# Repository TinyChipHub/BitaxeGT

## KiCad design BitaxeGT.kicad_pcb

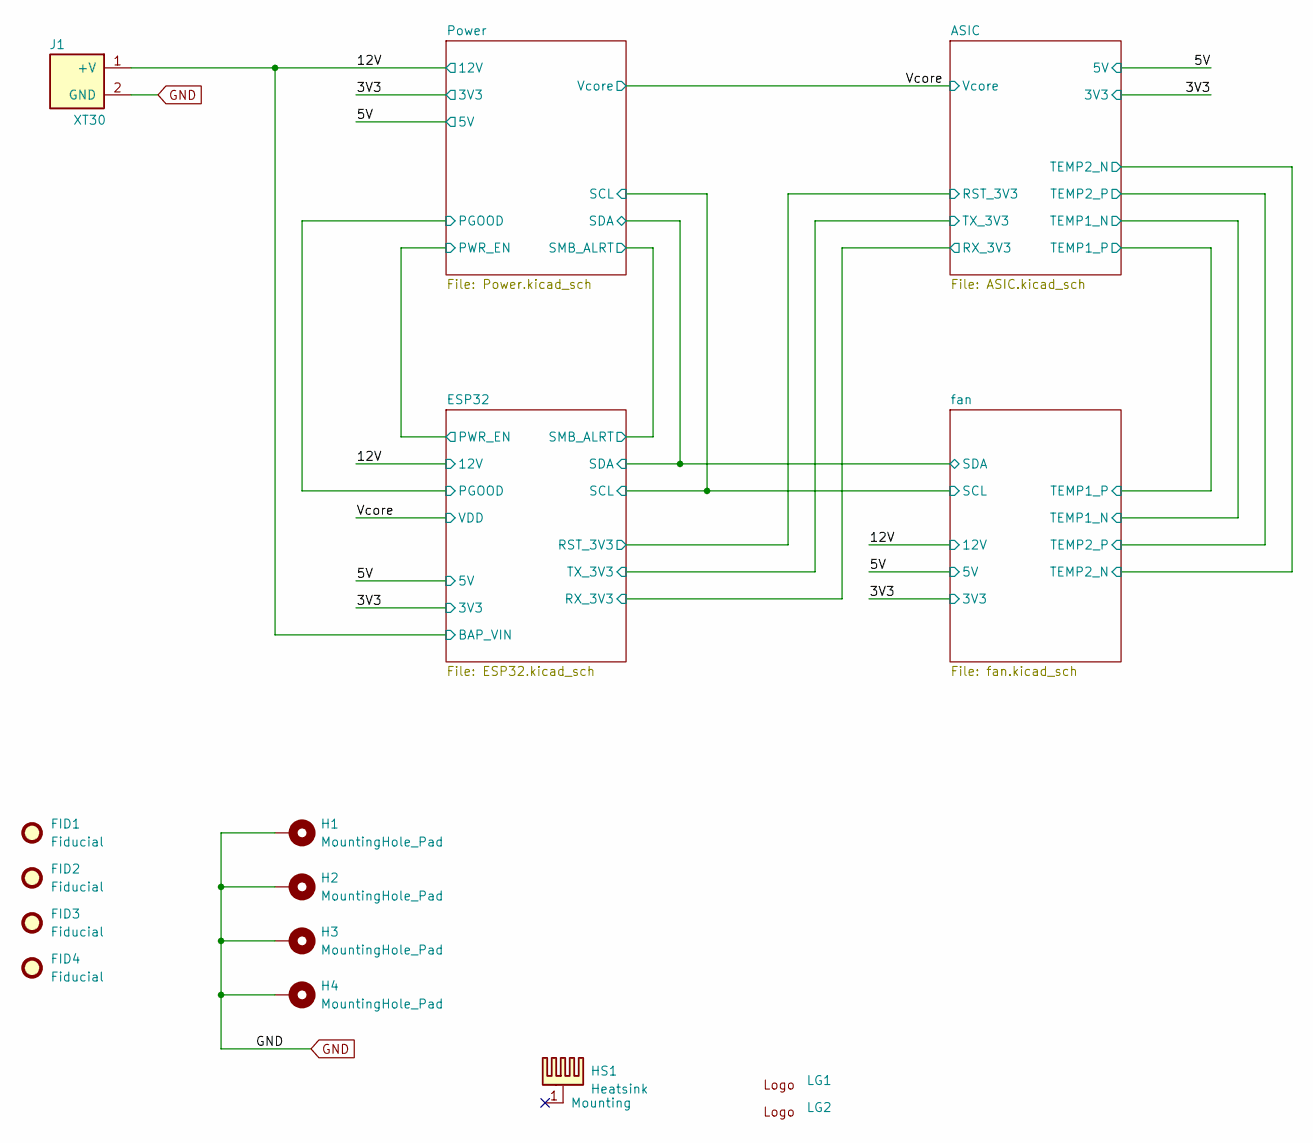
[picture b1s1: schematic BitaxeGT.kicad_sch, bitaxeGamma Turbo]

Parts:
FID1, FID2, FID3, FID4: Fiducial; Fiducial_1mm_Mask2mm
H1, H2, H3, H4: MountingHole_Pad; MountingHole_3.2mm_M3_Pad_Via
HS1: Heatsink; Heatsink-BitaxeGT
J1: XT30; XT30PW-M; PARTNO XT30PW-M; LCSC C431092
LG1: TCH-Logo
LG2: TCH-Logo-Mask

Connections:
/12V: J1.1 (+V); also elsewhere on the board
GND: H1.1, H2.1, H3.1, H4.1, J1.2 (GND); also elsewhere on the board

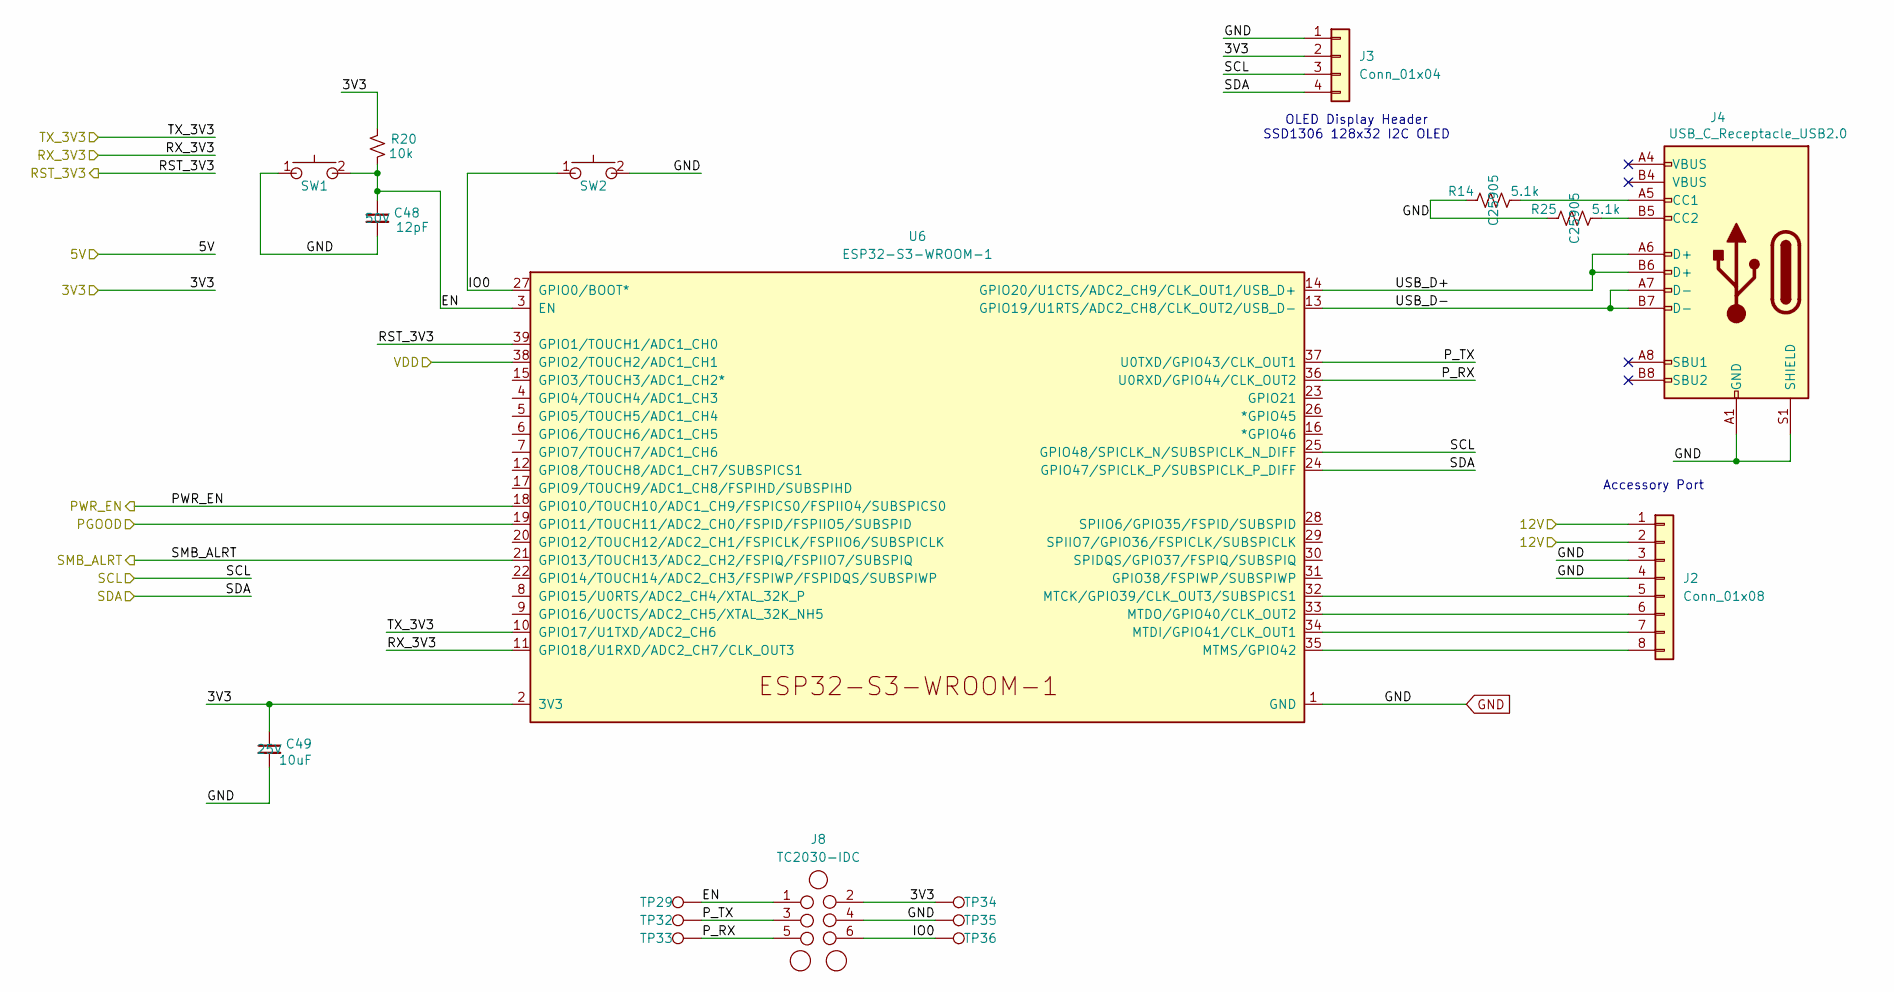
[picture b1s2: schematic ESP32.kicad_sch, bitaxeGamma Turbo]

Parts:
C48: 12pF; C_0402_1005Metric; Voltage 50V; PARTNO CC0402JRNPO9BN120; LCSC C106201
C49: 10uF; C_0603_1608Metric; Voltage 25V; PARTNO GRM188R61E106KA73D; LCSC C344022
J2: Conn_01x08; FPC-SMD_P0.50-8P_FGS-XJ-H2.0; PARTNO FFC2B35-08-T; LCSC C262657
J3: Conn_01x04; PinHeader_1x04_P2.54mm_Vertical_shifted
J4: USB_C_Receptacle_USB2.0; USB_C_Receptacle_GCT_USB4105-xx-A; PARTNO USB4105-GF-A; LCSC C2982555
J8: TC2030-IDC; Tag-Connect_TC2030-IDC-NL_2x03_P1.27mm_Vertical
R14, R25: 5.1k; R_0402_1005Metric; PARTNO RMCF0402JT5K10; LCSC C25905
R20: 10k; R_0402_1005Metric; PARTNO RC0402JR-0710KL; LCSC C60489
SW1, SW2: SWITCH-SPST; SW_TL3330AF130QG_EWI; PARTNO TL3330AF130QG; LCSC C2886885
TP29, TP32, TP33, TP34, TP35, TP36: TestPoint; TestPoint_Pad_D1.5mm
U6: ESP32-S3-WROOM-1; PARTNO ESP32-S3-WROOM-1-N16R8; LCSC C2913202

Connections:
/3V3: C49.1, J3.2, J8.2, R20.2, TP34.1, U6.2 (3V3); also elsewhere on the board
/12V: J2.1, J2.2; also elsewhere on the board
/ASIC/RST_3V3: U6.39 (GPIO1/TOUCH1/ADC1_CH0); also elsewhere on the board
/ASIC/RX_3V3: U6.11 (GPIO18/U1RXD/ADC2_CH7/CLK_OUT3); also elsewhere on the board
/ASIC/TX_3V3: U6.10 (GPIO17/U1TXD/ADC2_CH6); also elsewhere on the board
/ESP32/EN: C48.1, J8.1, R20.1, SW1.2, TP29.1, U6.3 (EN)
/ESP32/IO0: J8.6, SW2.1, TP36.1, U6.27 (GPIO0/BOOT*)
/ESP32/PWR_EN: U6.18 (GPIO10/TOUCH10/ADC1_CH9/FSPICS0/FSPIIO4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)
/ESP32/P_RX: J8.5, TP33.1, U6.36 (U0RXD/GPIO44/CLK_OUT2)
/ESP32/P_TX: J8.3, TP32.1, U6.37 (U0TXD/GPIO43/CLK_OUT1)
/ESP32/SCL: J3.3, U6.25 (GPIO48/SPICLK_N/SUBSPICLK_N_DIFF); also elsewhere on the board
/ESP32/SDA: J3.4, U6.24 (GPIO47/SPICLK_P/SUBSPICLK_P_DIFF); also elsewhere on the board
/ESP32/SMB_ALRT: U6.21 (GPIO13/TOUCH13/ADC2_CH2/FSPIQ/FSPIIO7/S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); also elsewhere on the board
/ESP32/USB_D+: J4.A6 (D+), J4.B6 (D+), U6.14 (GPIO20/U1CTS/ADC2_CH9/CLK_OUT1/USB_D+)
/ESP32/USB_D-: J4.A7 (D-), J4.B7 (D-), U6.13 (GPIO19/U1RTS/ADC2_CH8/CLK_OUT2/USB_D-)
/Power/PGOOD: U6.19 (GPIO11/TOUCH11/ADC2_CH0/FSPID/FSPIIO5/S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); also elsewhere on the board
/Vcore: U6.38 (GPIO2/TOUCH2/ADC1_CH1); also elsewhere on the board
GND: C48.2, C49.2, J2.3, J2.4, J3.1, J4.A1 (GND), J4.B1 (GND), J4.S1 (SHIELD), J8.4, R14.1, R25.1, SW1.1, SW2.2, TP35.1, U6.1 (GND), U6.40 (GND), U6.41 (GND); also elsewhere on the board
unnamed: J2.5, U6.32 (MTCK/GPIO39/CLK_OUT3/SUBSPICS1)
unnamed: J2.6, U6.33 (MTDO/GPIO40/CLK_OUT2)
unnamed: J2.7, U6.34 (MTDI/GPIO41/CLK_OUT1)
unnamed: J2.8, U6.35 (MTMS/GPIO42)
unnamed: J4.A5 (CC1), R14.2
unnamed: J4.B5 (CC2), R25.2

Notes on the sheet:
OLED Display Header SSD1306 128x32 I2C OLED
Accessory Port

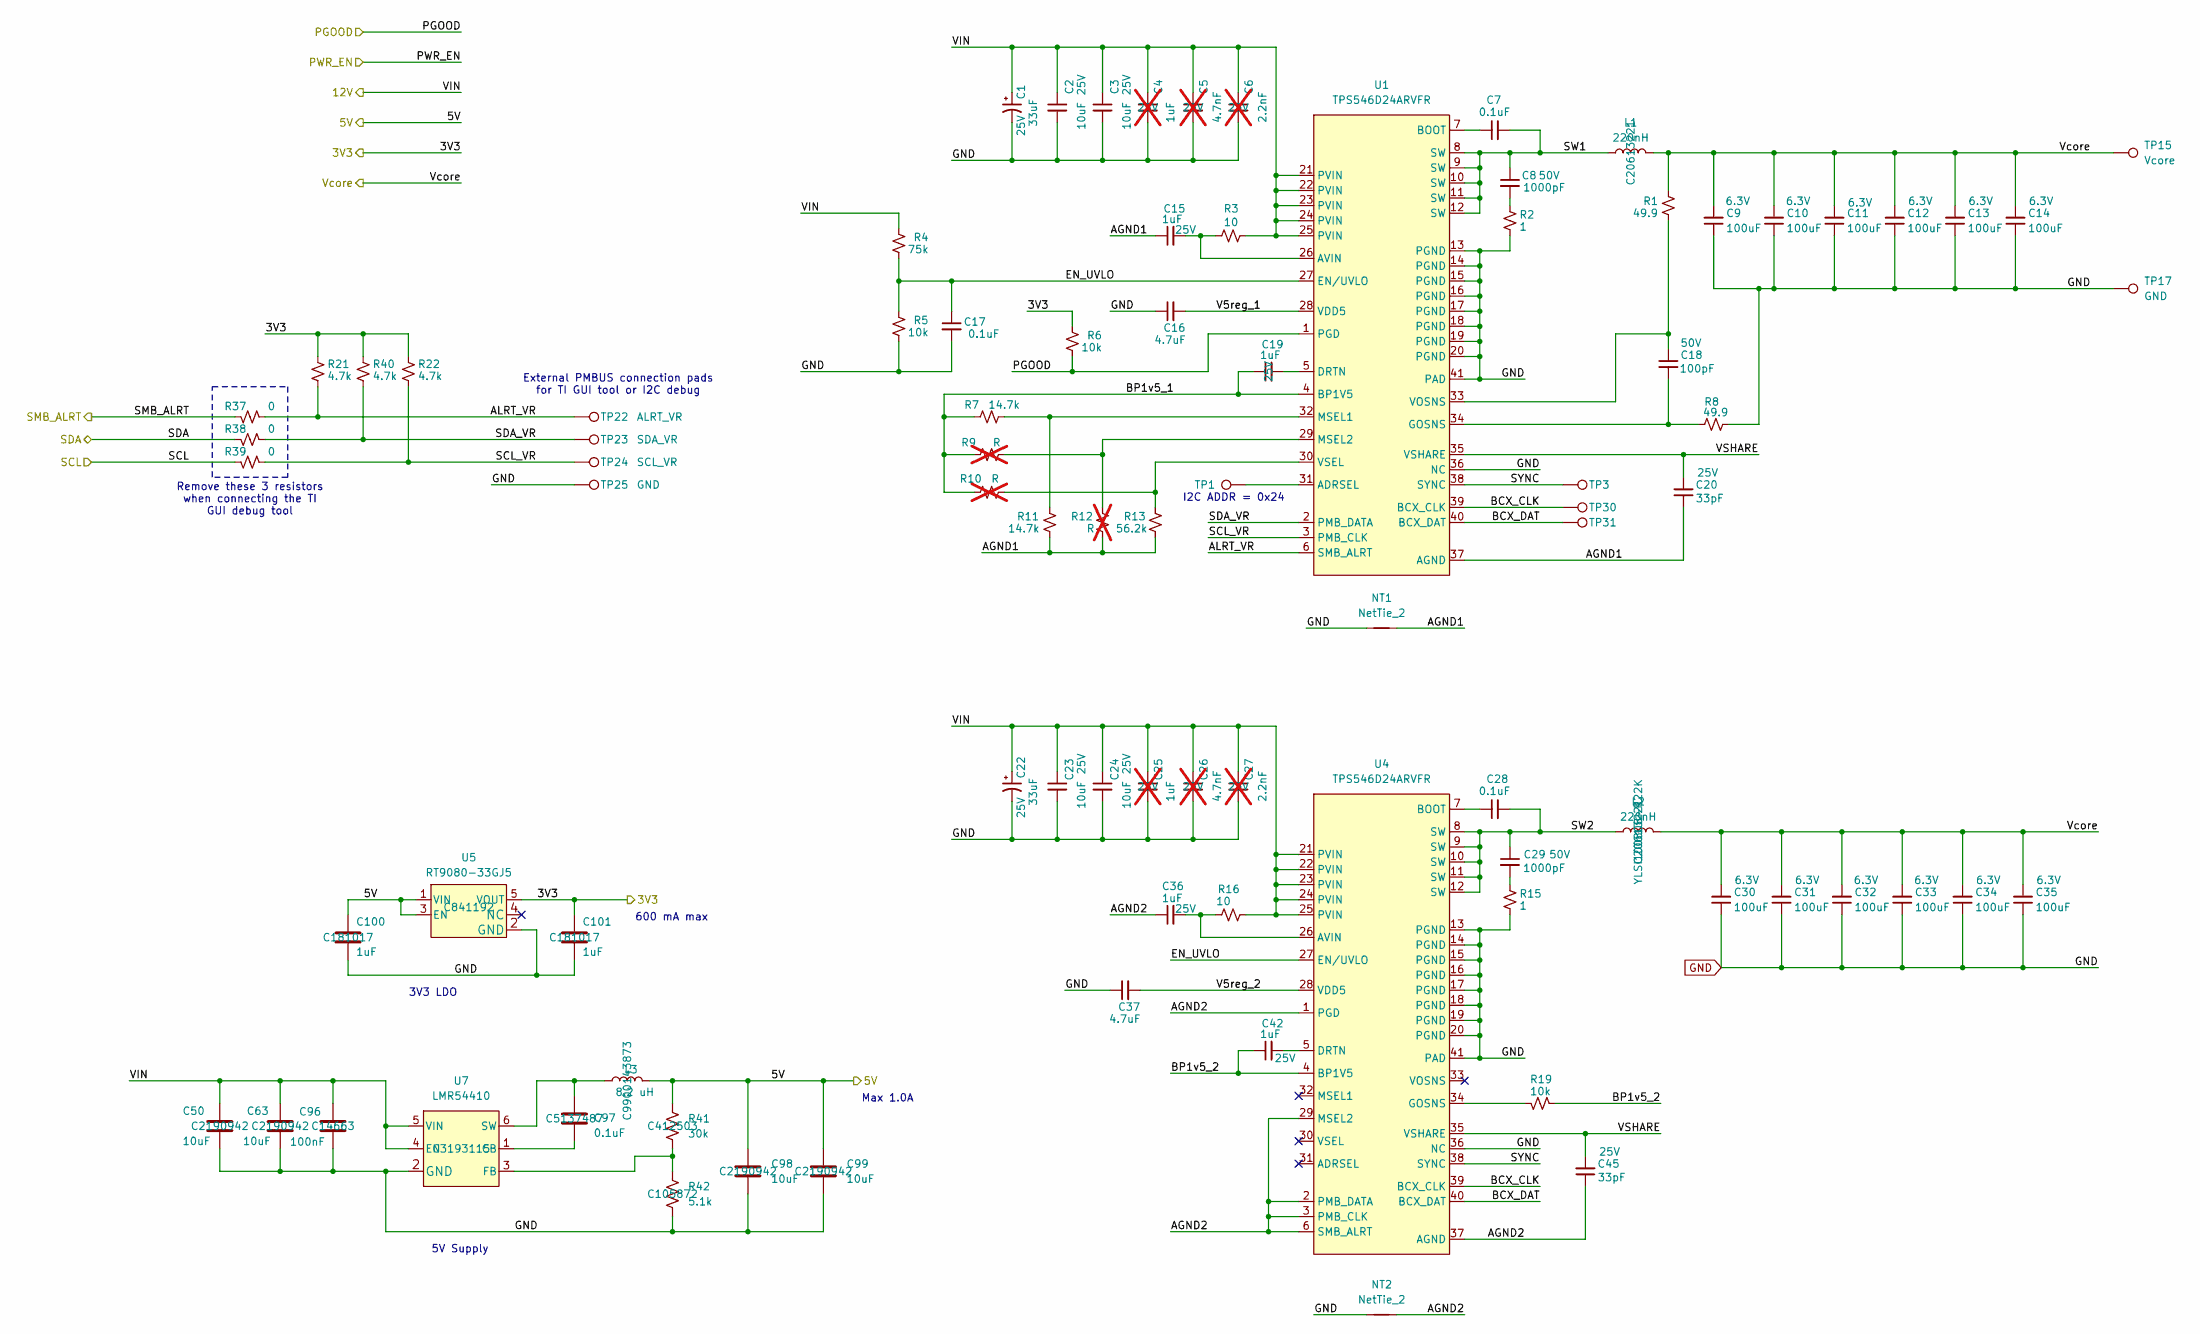
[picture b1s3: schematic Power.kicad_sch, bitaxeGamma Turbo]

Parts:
C1, C22: 33uF; CP_EIA-7343-31_Kemet-D; Voltage 25V; PARTNO T495D336K025ATE300; LCSC C122327
C2, C3, C23, C24: 10uF; C_0603_1608Metric; Voltage 25V; PARTNO GRM188R61E106KA73D; LCSC C344022
C4, C25: 1uF; C_0402_1005Metric; Voltage 25V; PARTNO TMK107B7105KA-T; not fitted
C5, C26: 4.7nF; C_0402_1005Metric; Voltage 25V; PARTNO GRM155R71E472KA01D; not fitted
C6, C27: 2.2nF; C_0402_1005Metric; Voltage 25V; PARTNO 490-8257-1-ND; not fitted
C7, C17, C28, C97: 0.1uF; C_0402_1005Metric; PARTNO KGM05AR71C104KH; LCSC C5137487
C8, C29: 1000pF; C_0805_2012Metric; Voltage 50V; PARTNO CC0805KRX7R9BB102; LCSC C46653
C9, C10, C11, C12, C13, C14, C30, C31, C32, C33, C34, C35: 100uF; C_1206_3216Metric; Voltage 6.3V; PARTNO CL31A107MQHNNNE; LCSC C15008
C15, C19, C36, C42: 1uF; C_0402_1005Metric; Voltage 25V; PARTNO TMK107B7105KA-T; LCSC C77009
C16, C37: 4.7uF; C_0402_1005Metric; PARTNO GRM155R61A475MEAAD; LCSC C23733
C18: 100pF; C_0402_1005Metric; Voltage 50V; PARTNO CC0402JRNPO9BN101; LCSC C277520
C20, C45: 33pF; C_0402_1005Metric; Voltage 25V; PARTNO KGM05ACG1E330JH; LCSC C526997
C50, C63, C98, C99: 10uF; C_0805_2012Metric; PARTNO GRM21BR61H106ME43L; LCSC C2190942
C96: 100nF; C_0603_1608Metric; PARTNO KGM15BR71H104KT; LCSC C14663
C100, C101: 1uF; C_0402_1005Metric; PARTNO EMK105BJ105MV-F; LCSC C181017
L1, L2: 220nH; SLC1175-271MEC_COC; PARTNO YLSI100808-R22K; LCSC C20613221
L3: 8.2 uH; 74438357082; PARTNO 78438357082; LCSC C9900143873
NT1, NT2: NetTie_2; NetTie-2_SMD_Pad0.2mmx1mm
R1, R8: 49.9; R_0402_1005Metric; PARTNO RC0402FR-0749R9L; LCSC C87044
R2, R15: 1; R_0805_2012Metric; PARTNO ESR10EZPJ1R0; LCSC C253344
R3, R16: 10; R_0402_1005Metric; PARTNO RC0402FR-0710RL; LCSC C138066
R4: 75k; R_0402_1005Metric; PARTNO RC0402FR-0775KL; LCSC C137935
R5, R6, R19: 10k; R_0402_1005Metric; PARTNO RC0402JR-0710KL; LCSC C60489
R7, R11: 14.7k; R_0402_1005Metric; PARTNO AC0402FR-0714K7L; LCSC C138055
R9, R10, R12: R; R_0402_1005Metric; not fitted
R13: 56.2k; R_0402_1005Metric; PARTNO RC0402FR-0756K2L; LCSC C183355
R21, R22, R40: 4.7k; R_0402_1005Metric; PARTNO RC0402JR-074K7L; LCSC C105870
R37, R38, R39: 0; R_0402_1005Metric; PARTNO RC0402JR-070RL; LCSC C60485
R41: 30k; R_0402_1005Metric; PARTNO AC0402FR-0730KL; LCSC C412503
R42: 5.1k; R_0402_1005Metric; PARTNO RC0402FR-075K1L; LCSC C105872
TP1: TestPoint; TestPoint_Pad_D1.0mm
TP3, TP30: BCX_CLK; TestPoint_Pad_D1.0mm
TP15: Vcore; TestPoint_Pad_D1.5mm
TP17, TP25: GND; TestPoint_Pad_D1.5mm
TP22: ALRT_VR; TestPoint_Pad_D1.5mm
TP23: SDA_VR; TestPoint_Pad_D1.5mm
TP24: SCL_VR; TestPoint_Pad_D1.5mm
TP31: BCX_DAT; TestPoint_Pad_D1.0mm
U1, U4: TPS546D24ARVFR; LQFN40-CLIP; PARTNO TPS546D24ARVFR; LCSC C507280
U5: RT9080-33GJ5; PARTNO RT9080-33GJ5; LCSC C841192
U7: LMR54410; SOT-23-6; PARTNO LMR54410FDBVR; LCSC C3193115

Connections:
/3V3: C101.1, R6.2, R21.1, R22.1, R40.1, U5.5 (VOUT); also elsewhere on the board
/5V: C98.1, C99.1, C100.1, L3.2, R41.1, U5.1 (VIN), U5.3 (EN); also elsewhere on the board
/12V: C1.1, C2.1, C3.1, C4.1, C5.1, C6.1, C22.1, C23.1, C24.1, C25.1, C26.1, C27.1, C50.1, C63.1, C96.2, R3.1, R4.2, R16.1, U1.21 (PVIN), U1.22 (PVIN), U1.23 (PVIN), U1.24 (PVIN), U1.25 (PVIN), U4.21 (PVIN), U4.22 (PVIN), U4.23 (PVIN), U4.24 (PVIN), U4.25 (PVIN), U7.4 (EN), U7.5 (VIN); also elsewhere on the board
/ESP32/SCL: R39.1; also elsewhere on the board
/ESP32/SDA: R38.1; also elsewhere on the board
/ESP32/SMB_ALRT: R37.1; also elsewhere on the board
/Power/AGND1: C15.1, C20.1, NT1.2, R11.2, R12.1, R13.1, U1.37 (AGND)
/Power/AGND2: C36.1, C45.1, NT2.2, U4.1 (PGD), U4.2 (PMB_DATA), U4.3 (PMB_CLK), U4.6 (SMB_ALRT), U4.29 (MSEL2), U4.37 (AGND)
/Power/ALRT_VR: R21.2, R37.2, TP22.1, U1.6 (SMB_ALRT)
/Power/BCX_CLK: TP30.1, U1.39 (BCX_CLK), U4.39 (BCX_CLK)
/Power/BCX_DAT: TP31.1, U1.40 (BCX_DAT), U4.40 (BCX_DAT)
/Power/BP1v5_1: C19.1, R7.2, R9.2, R10.2, U1.4 (BP1V5)
/Power/BP1v5_2: C42.1, R19.1, U4.4 (BP1V5)
/Power/EN_UVLO: C17.1, R4.1, R5.2, U1.27 (EN/UVLO), U4.27 (EN/UVLO)
/Power/PGOOD: R6.1, U1.1 (PGD); also elsewhere on the board
/Power/SCL_VR: R22.2, R39.2, TP24.1, U1.3 (PMB_CLK)
/Power/SDA_VR: R38.2, R40.2, TP23.1, U1.2 (PMB_DATA)
/Power/SW1: C7.2, C8.1, L1.1, U1.8 (SW), U1.9 (SW), U1.10 (SW), U1.11 (SW), U1.12 (SW)
/Power/SW2: C28.2, C29.1, L2.1, U4.8 (SW), U4.9 (SW), U4.10 (SW), U4.11 (SW), U4.12 (SW)
/Power/SYNC: TP3.1, U1.38 (SYNC), U4.38 (SYNC)
/Power/V5reg_1: C16.2, U1.28 (VDD5)
/Power/V5reg_2: C37.2, U4.28 (VDD5)
/Power/VSHARE: C20.2, C45.2, U1.35 (VSHARE), U4.35 (VSHARE)
/Vcore: C9.2, C10.2, C11.2, C12.2, C13.2, C14.2, C30.2, C31.2, C32.2, C33.2, C34.2, C35.2, L1.2, L2.2, R1.1, TP15.1; also elsewhere on the board
GND: C1.2, C2.2, C3.2, C4.2, C5.2, C6.2, C9.1, C10.1, C11.1, C12.1, C13.1, C14.1, C16.1, C17.2, C22.2, C23.2, C24.2, C25.2, C26.2, C27.2, C30.1, C31.1, C32.1, C33.1, C34.1, C35.1, C37.1, C50.2, C63.2, C96.1, C98.2, C99.2, C100.2, C101.2, NT1.1, NT2.1, R2.2, R5.1, R8.2, R15.2, R42.2, TP17.1, TP25.1, U1.13 (PGND), U1.14 (PGND), U1.15 (PGND), U1.16 (PGND), U1.17 (PGND), U1.18 (PGND), U1.19 (PGND), U1.20 (PGND), U1.36 (NC), U1.41 (PAD), U4.13 (PGND), U4.14 (PGND), U4.15 (PGND), U4.16 (PGND), U4.17 (PGND), U4.18 (PGND), U4.19 (PGND), U4.20 (PGND), U4.36 (NC), U4.41 (PAD), U5.2 (GND), U7.2 (GND); also elsewhere on the board
unnamed: C8.2, R2.1
unnamed: C29.2, R15.1
unnamed: TP1.1, U1.31 (ADRSEL)
unnamed: C15.2, R3.2, U1.26 (AVIN)
unnamed: C7.1, U1.7 (BOOT)
unnamed: C19.2, U1.5 (DRTN)
unnamed: C18.2, R8.1, U1.34 (GOSNS)
unnamed: R7.1, R11.1, U1.32 (MSEL1)
unnamed: R9.1, R12.2, U1.29 (MSEL2)
unnamed: C18.1, R1.2, U1.33 (VOSNS)
unnamed: R10.1, R13.2, U1.30 (VSEL)
unnamed: C36.2, R16.2, U4.26 (AVIN)
unnamed: C28.1, U4.7 (BOOT)
unnamed: C42.2, U4.5 (DRTN)
unnamed: R19.2, U4.34 (GOSNS)
unnamed: C97.2, U7.1 (CB)
unnamed: R41.2, R42.1, U7.3 (FB)
unnamed: C97.1, L3.1, U7.6 (SW)

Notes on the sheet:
External PMBUS connection pads for TI GUI tool or I2C debug
Max 1.0A
3V3 LDO
Remove these 3 resistors when connecting the TI GUI debug tool
I2C ADDR = 0x24
600 mA max
5V Supply

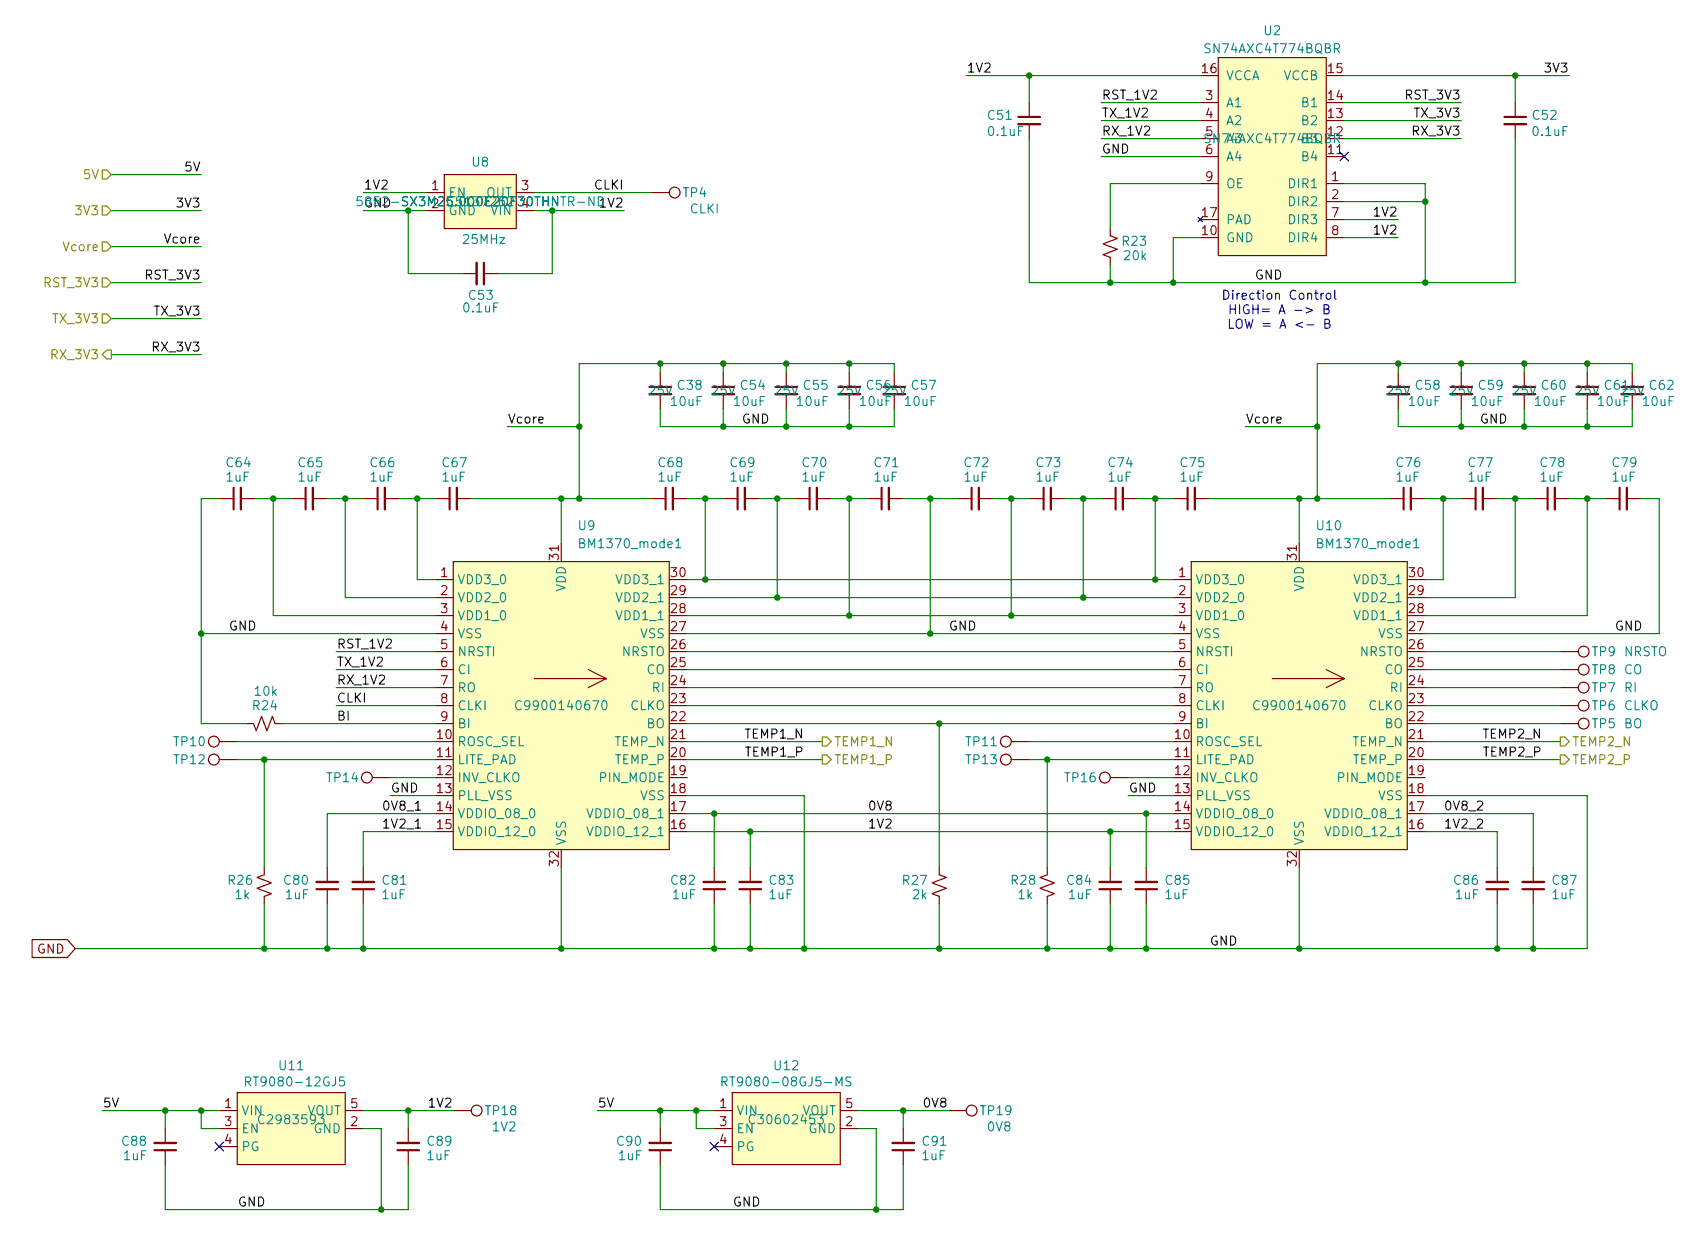
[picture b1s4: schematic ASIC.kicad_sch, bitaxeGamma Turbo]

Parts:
C38, C54, C55, C56, C57, C58, C59, C60, C61, C62: 10uF; C_0603_1608Metric; Voltage 25V; PARTNO GRM188R61E106KA73D; LCSC C344022
C51, C52, C53: 0.1uF; C_0402_1005Metric; PARTNO KGM05AR71C104KH; LCSC C5137487
C64, C65, C66, C67, C68, C69, C70, C71, C72, C73, C74, C75, C76, C77, C78, C79, C80, C81, C82, C83, C84, C85, C86, C87, C88, C89, C90, C91: 1uF; C_0402_1005Metric; PARTNO EMK105BJ105MV-F; LCSC C181017
R23: 20k; R_0402_1005Metric; PARTNO RC0402FR-0720KL; LCSC C93942
R24: 10k; R_0402_1005Metric; PARTNO RC0402JR-0710KL; LCSC C60489
R26, R28: 1k; R_0402_1005Metric; PARTNO RC0402FR-071KL; LCSC C106235
R27: 2k; R_0402_1005Metric; PARTNO RT0402BRD072KL; LCSC C852711
TP4: CLKI; TestPoint_Pad_D1.0mm
TP5: BO; TestPoint_Pad_D1.0mm
TP6: CLKO; TestPoint_Pad_D1.0mm
TP7: RI; TestPoint_Pad_D1.0mm
TP8: CO; TestPoint_Pad_D1.0mm
TP9: NRSTO; TestPoint_Pad_D1.0mm
TP10, TP11, TP12, TP13, TP14, TP16: TestPoint; TestPoint_Pad_D1.0mm
TP18: 1V2; TestPoint_Pad_D1.5mm
TP19: 0V8; TestPoint_Pad_D1.5mm
U2: SN74AXC4T774BQBR; BQB0016A-MFG; PARTNO SN74AXC4T774BQBR; LCSC C2862903
U8: 25MHz; SMD3225-4P; PARTNO SX3M25.000E20F30THN; LCSC C5137262
U9, U10: BM1370_mode1; BM1370; LCSC C9900140670
U11: RT9080-12GJ5; SOT-23-5; PARTNO MCP1824T-1202E/OT; LCSC C2983593
U12: RT9080-08GJ5-MS; SOT-23-5; PARTNO MCP1824T-0802E/OT; LCSC C30602453

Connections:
/3V3: C52.1, U2.15 (VCCB); also elsewhere on the board
/5V: C88.2, C90.2, U11.1 (VIN), U11.3 (EN), U12.1 (VIN), U12.3 (EN); also elsewhere on the board
/ASIC/0V8: C82.2, C85.2, C91.2, TP19.1, U9.17 (VDDIO_08_1), U10.14 (VDDIO_08_0), U12.5 (VOUT)
/ASIC/0V8_1: C80.2, U9.14 (VDDIO_08_0)
/ASIC/0V8_2: C87.2, U10.17 (VDDIO_08_1)
/ASIC/1V2: C51.1, C53.1, C83.2, C84.2, C89.2, TP18.1, U2.7 (DIR3), U2.8 (DIR4), U2.16 (VCCA), U8.1 (EN), U8.4 (VIN), U9.16 (VDDIO_12_1), U10.15 (VDDIO_12_0), U11.5 (VOUT)
/ASIC/1V2_1: C81.2, U9.15 (VDDIO_12_0)
/ASIC/1V2_2: C86.2, U10.16 (VDDIO_12_1)
/ASIC/BI: R24.2, U9.9 (BI)
/ASIC/CLKI: TP4.1, U8.3 (OUT), U9.8 (CLKI)
/ASIC/RST_1V2: U2.3 (A1), U9.5 (NRSTI)
/ASIC/RST_3V3: U2.14 (B1); also elsewhere on the board
/ASIC/RX_1V2: U2.5 (A3), U9.7 (RO)
/ASIC/RX_3V3: U2.12 (B3); also elsewhere on the board
/ASIC/TEMP1_N: U9.21 (TEMP_N); also elsewhere on the board
/ASIC/TEMP1_P: U9.20 (TEMP_P); also elsewhere on the board
/ASIC/TEMP2_N: U10.21 (TEMP_N); also elsewhere on the board
/ASIC/TEMP2_P: U10.20 (TEMP_P); also elsewhere on the board
/ASIC/TX_1V2: U2.4 (A2), U9.6 (CI)
/ASIC/TX_3V3: U2.13 (B2); also elsewhere on the board
/Vcore: C38.1, C54.1, C55.1, C56.1, C57.1, C58.1, C59.1, C60.1, C61.1, C62.1, C67.2, C68.1, C75.2, C76.1, U9.31 (VDD), U10.31 (VDD); also elsewhere on the board
GND: C38.2, C51.2, C52.2, C53.2, C54.2, C55.2, C56.2, C57.2, C58.2, C59.2, C60.2, C61.2, C62.2, C64.1, C71.2, C72.1, C79.2, C80.1, C81.1, C82.1, C83.1, C84.1, C85.1, C86.1, C87.1, C88.1, C89.1, C90.1, C91.1, R23.1, R24.1, R26.1, R27.1, R28.1, U2.1 (DIR1), U2.2 (DIR2), U2.6 (A4), U2.10 (GND), U8.2 (GND), U9.4 (VSS), U9.13 (PLL_VSS), U9.18 (VSS), U9.27 (VSS), U9.32 (VSS), U10.4 (VSS), U10.13 (PLL_VSS), U10.18 (VSS), U10.27 (VSS), U10.32 (VSS), U11.2 (GND), U12.2 (GND); also elsewhere on the board
unnamed: R23.2, U2.9 (OE)
unnamed: TP14.1, U9.12 (INV_CLKO)
unnamed: R26.2, TP12.1, U9.11 (LITE_PAD)
unnamed: TP10.1, U9.10 (ROSC_SEL)
unnamed: C64.2, C65.1, U9.3 (VDD1_0)
unnamed: C65.2, C66.1, U9.2 (VDD2_0)
unnamed: C66.2, C67.1, U9.1 (VDD3_0)
unnamed: R27.2, U9.22 (BO), U10.9 (BI)
unnamed: TP5.1, U10.22 (BO)
unnamed: U9.25 (CO), U10.6 (CI)
unnamed: U9.23 (CLKO), U10.8 (CLKI)
unnamed: TP6.1, U10.23 (CLKO)
unnamed: TP8.1, U10.25 (CO)
unnamed: TP16.1, U10.12 (INV_CLKO)
unnamed: R28.2, TP13.1, U10.11 (LITE_PAD)
unnamed: U9.26 (NRSTO), U10.5 (NRSTI)
unnamed: TP9.1, U10.26 (NRSTO)
unnamed: TP7.1, U10.24 (RI)
unnamed: U9.24 (RI), U10.7 (RO)
unnamed: TP11.1, U10.10 (ROSC_SEL)
unnamed: C70.2, C71.1, C72.2, C73.1, U9.28 (VDD1_1), U10.3 (VDD1_0)
unnamed: C78.2, C79.1, U10.28 (VDD1_1)
unnamed: C69.2, C70.1, C73.2, C74.1, U9.29 (VDD2_1), U10.2 (VDD2_0)
unnamed: C77.2, C78.1, U10.29 (VDD2_1)
unnamed: C68.2, C69.1, C74.2, C75.1, U9.30 (VDD3_1), U10.1 (VDD3_0)
unnamed: C76.2, C77.1, U10.30 (VDD3_1)

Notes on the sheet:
Direction Control HIGH= A -> B LOW = A <- B

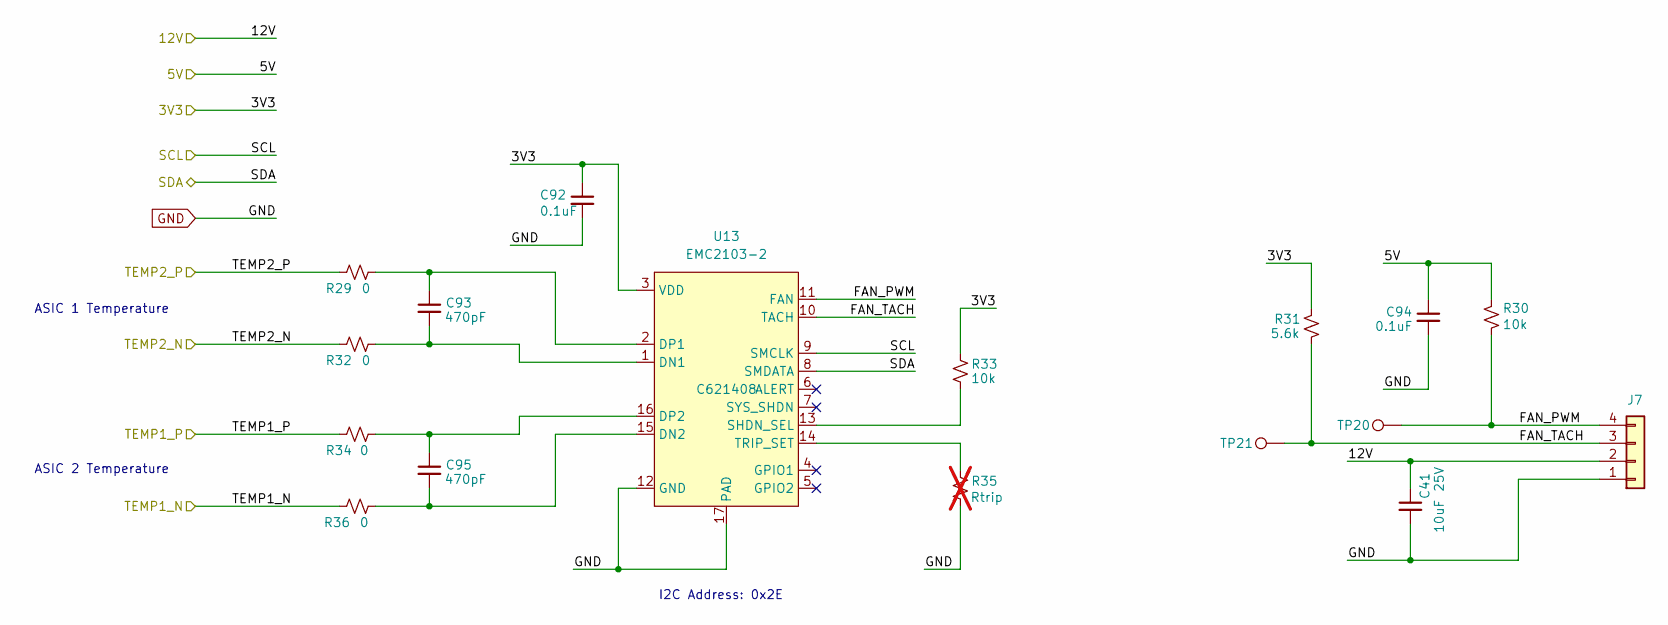
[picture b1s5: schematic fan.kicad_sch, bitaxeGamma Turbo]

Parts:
C41: 10uF; C_0603_1608Metric; Voltage 25V; PARTNO GRM188R61E106KA73D; LCSC C344022
C92, C94: 0.1uF; C_0402_1005Metric; PARTNO KGM05AR71C104KH; LCSC C5137487
C93, C95: 470pF; C_0402_1005Metric; PARTNO GRM1555C1H471JA01D; LCSC C76971
J7: Conn_01x04; 470531000; PARTNO 0470531000; LCSC C240840
R29, R32, R34, R36: 0; R_0402_1005Metric; PARTNO RC0402JR-070RL; LCSC C60485
R30, R33: 10k; R_0402_1005Metric; PARTNO RC0402JR-0710KL; LCSC C60489
R31: 5.6k; R_0402_1005Metric; PARTNO RC0402FR-075K6L; LCSC C163457
R35: Rtrip; R_0402_1005Metric; not fitted
TP20, TP21: TestPoint; TestPoint_Pad_D1.0mm
U13: EMC2103-2; QFN-16-1EP_4x4mm_P0.65mm_EP2.1x2.1mm; PARTNO EMC2103-4-AP-TR; LCSC C621408

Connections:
/3V3: C92.1, R31.2, R33.2, U13.3 (VDD); also elsewhere on the board
/5V: C94.1, R30.2; also elsewhere on the board
/12V: C41.1, J7.2; also elsewhere on the board
/ASIC/TEMP1_N: R36.2; also elsewhere on the board
/ASIC/TEMP1_P: R34.2; also elsewhere on the board
/ASIC/TEMP2_N: R32.2; also elsewhere on the board
/ASIC/TEMP2_P: R29.2; also elsewhere on the board
/ESP32/SCL: U13.9 (SMCLK); also elsewhere on the board
/ESP32/SDA: U13.8 (SMDATA); also elsewhere on the board
/fan/FAN_PWM: J7.4, R30.1, TP20.1, U13.11 (FAN)
/fan/FAN_TACH: J7.3, R31.1, TP21.1, U13.10 (TACH)
GND: C41.2, C92.2, C94.2, J7.1, R35.1, U13.12 (GND), U13.17 (PAD); also elsewhere on the board
unnamed: C93.2, R32.1, U13.1 (DN1)
unnamed: C95.2, R36.1, U13.15 (DN2)
unnamed: C93.1, R29.1, U13.2 (DP1)
unnamed: C95.1, R34.1, U13.16 (DP2)
unnamed: R33.1, U13.13 (SHDN_SEL)
unnamed: R35.2, U13.14 (TRIP_SET)

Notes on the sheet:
I2C Address: 0x2E
ASIC 2 Temperature
ASIC 1 Temperature

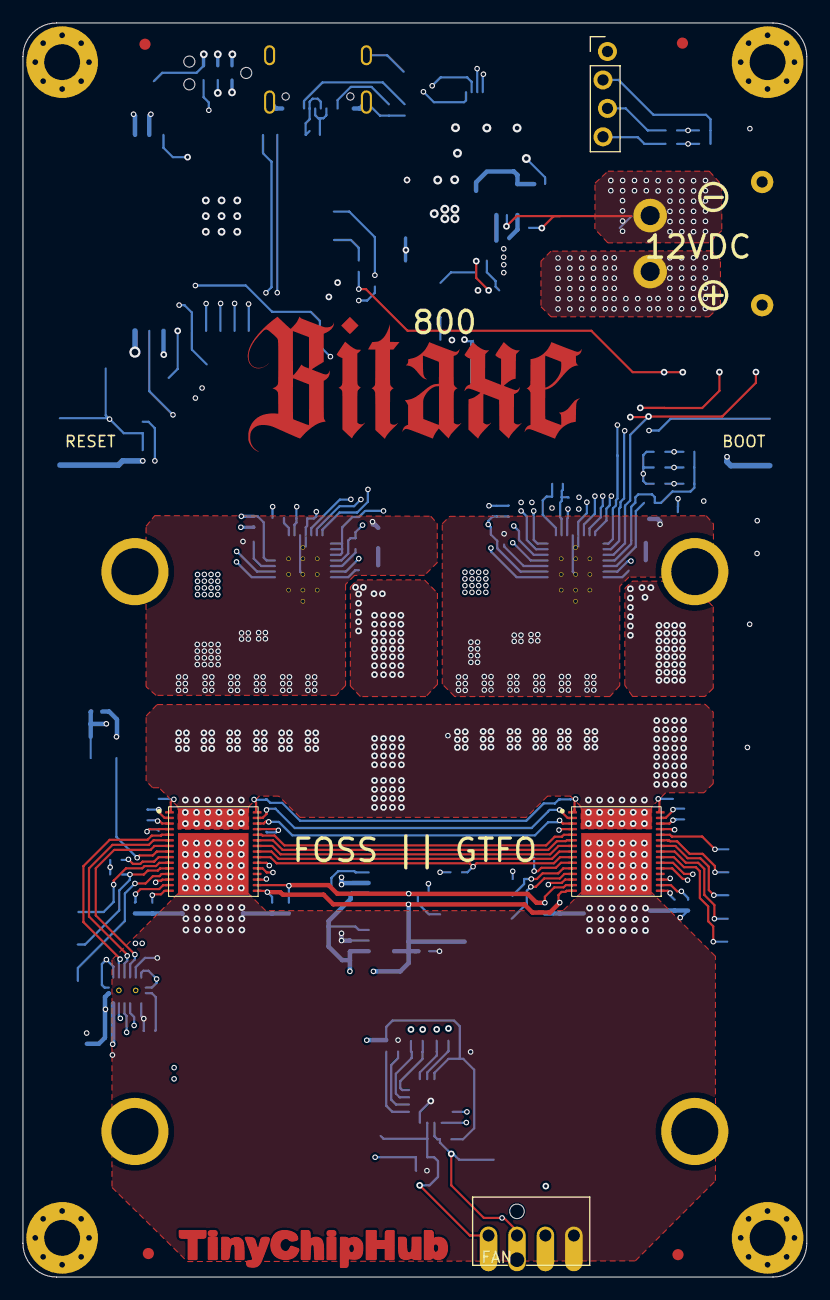
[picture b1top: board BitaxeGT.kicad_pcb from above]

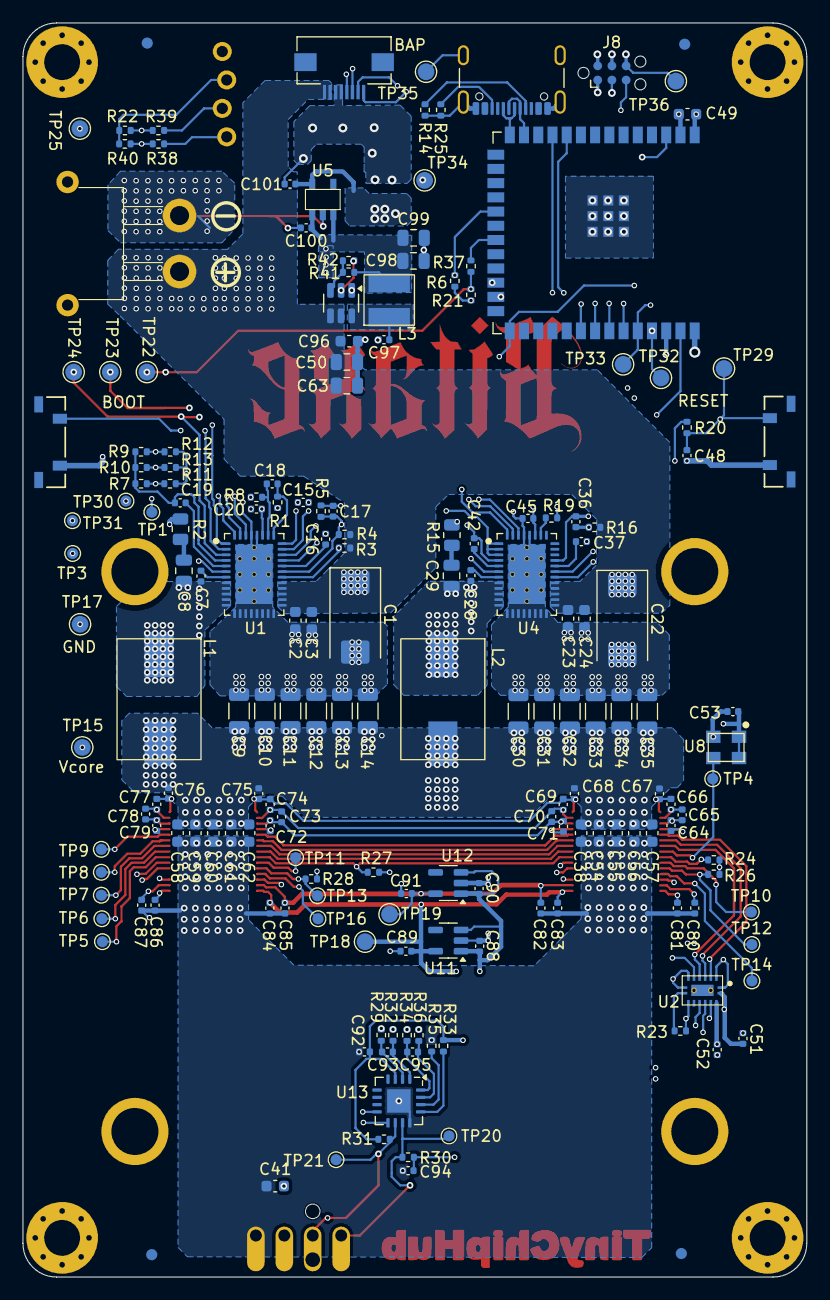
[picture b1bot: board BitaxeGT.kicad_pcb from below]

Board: 6 copper layers, 70.0 x 112.0 mm, 196 parts (183 on the bottom side), 107 nets.

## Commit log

2025-09-13 add TCH logo
2025-09-13 add LCSC code
2025-09-16 Start changing ldo to match our production
2025-09-16 final update
2025-09-16 change cap
2025-09-27 tune component positions
